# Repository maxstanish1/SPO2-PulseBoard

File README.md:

# SPO2-PulseBoard
A custom heart rate and SpO2 monitor built on an Arduino Uno R3 with a MAX30105 sensor and SSD1306 OLED display. Features a custom PCB, mode-switching buttons, and an alarm LED. Uses lightweight R-ratio SpO2 calculation and peak-detection heart rate — all tuned to run within the Arduino Uno's RAM limits.

# PulseBoard

A custom heart rate and SpO2 monitor built on an Arduino Uno R3 with a MAX30105 sensor and SSD1306 OLED display. Features a custom PCB, mode-switching buttons, and an alarm LED. Uses lightweight R-ratio SpO2 calculation and peak-detection heart rate — all tuned to run within the Arduino Uno's RAM limits.

---

## Hardware

| Component | Details |
|-----------|---------|
| Microcontroller | Arduino Uno R3 |
| Sensor | MAX30105 optical heart rate / SpO2 |
| Display | SSD1306 128×32 OLED (I2C) |
| PCB | Custom — see `/hardware` for Gerber files |

### Pin Map

| Pin | Function |
|-----|----------|
| D2 | Menu button — cycles between Heart Rate and SpO2 mode |
| D3 | Up button — reserved for future use |
| D4 | Down button — reserved for future use |
| D12 | Alarm LED — flashes when no finger is on the sensor |
| SDA / SCL | Shared I2C bus → MAX30105 + SSD1306 |

### Button Circuit
All three buttons are active-low, held HIGH by 1kΩ pull-up resistors (R1, R2, R3) with 100nF decoupling capacitors for hardware debounce. The alarm LED is driven through a 1kΩ current-limiting resistor (R4).

---

## Features

- **Heart Rate (BPM)** — peak detection on a rolling IR signal window with a 4-beat rolling average
- **SpO2 (%)** — R-ratio method with a quadratic calibration formula for accurate readings in the healthy range
- **Mode switching** — press D2 to toggle between Heart Rate and SpO2 mode; a splash screen confirms the switch
- **Alarm LED** — flashes at 1Hz on D12 when no finger is detected, turns off immediately when a finger is placed
- **Stable display** — 500ms refresh throttle prevents flicker; readings are held back for the first few seconds until the signal stabilizes

---

## How It Works

### Finger Detection
The sketch polls the MAX30105 every loop. An IR value above 50,000 indicates a finger is present (tissue absorbs the light). Below that threshold, the sensor is reading open air. All HR and SpO2 state resets on each new finger placement.

### Heart Rate Detection
A 10-sample rolling window tracks the IR signal's min, max, and range. Beat detection fires when the signal crosses 50% of the range, subject to these parameters:

| Parameter | Value |
|-----------|-------|
| Threshold | 50% of signal range |
| Minimum signal range | 400 |
| Minimum time between beats | 400ms |
| First beat | Always skipped (timing invalid) |
| Valid BPM range | 50 – 120 |
| Rolling average | 4 beats |
| Avg display delay | 8 seconds |

### SpO2 Calculation
AC (peak-to-peak) and DC (midpoint) values are computed for both the Red and IR channels from the same 10-sample window. The R-ratio is calculated as:

```
R = (redAC / redDC) / (irAC / irDC)
```

R is then passed through a quadratic calibration formula fitted to empirical blood oxygen absorption data:

```
SpO2 = -45.060 × R² + 30.354 × R + 94.845
```

The result is clamped between 70–100% and smoothed with a 9-reading rolling average. Readings are displayed after 5 seconds.

> **Note:** This formula is accurate in the healthy range (95–100%). Readings below ~90% should be treated as approximate — the sensor is not designed for clinical low-SpO2 accuracy.

---

## Libraries Required

Install these through the Arduino IDE Library Manager before compiling:

- [Adafruit SSD1306](https://github.com/adafruit/Adafruit_SSD1306)
- [Adafruit GFX](https://github.com/adafruit/Adafruit-GFX-Library)
- [SparkFun MAX3010x](https://github.com/sparkfun/SparkFun_MAX3010x_Sensor_Library) — provides `MAX30105.h`

> **Note:** This project does NOT use `spo2_algorithm.h`. That library was tested but exceeded the Uno's available RAM. SpO2 logic here is a custom lightweight implementation.

---

## Usage

1. Wire up the hardware according to the pin map above or use the custom PCB
2. Install the required libraries
3. Upload `heart_monitor.ino` to your Arduino Uno R3
4. Place your finger **lightly** on the sensor — pressing too hard flattens the pulse waveform and stops beat detection
5. Press **D2** to switch between Heart Rate and SpO2 mode
6. Wait 8 seconds for a stable heart rate average, or 5 seconds for an SpO2 reading

---

## Known Limitations

- **Finger pressure is critical** — too much pressure drops the signal range below 400 and halts detection
- **INT pin unused** — the MAX30105 interrupt pin is wired on the PCB but unconnected in firmware. Currently the sketch polls the sensor every loop. Future enhancement: wire INT to D7 for event-driven reads
- **SpO2 accuracy** — reliable in the 95–100% range; not suitable for clinical use
- **BPM range** — capped at 50–120 BPM; athletes with resting HR below 50 will see no reading

---

## Project Structure

```
PulseBoard/
├── firmware/
│   └── heart_monitor.ino
├── hardware/
│   └── (Gerber files, schematic)
└── README.md
```

---

## License

MIT

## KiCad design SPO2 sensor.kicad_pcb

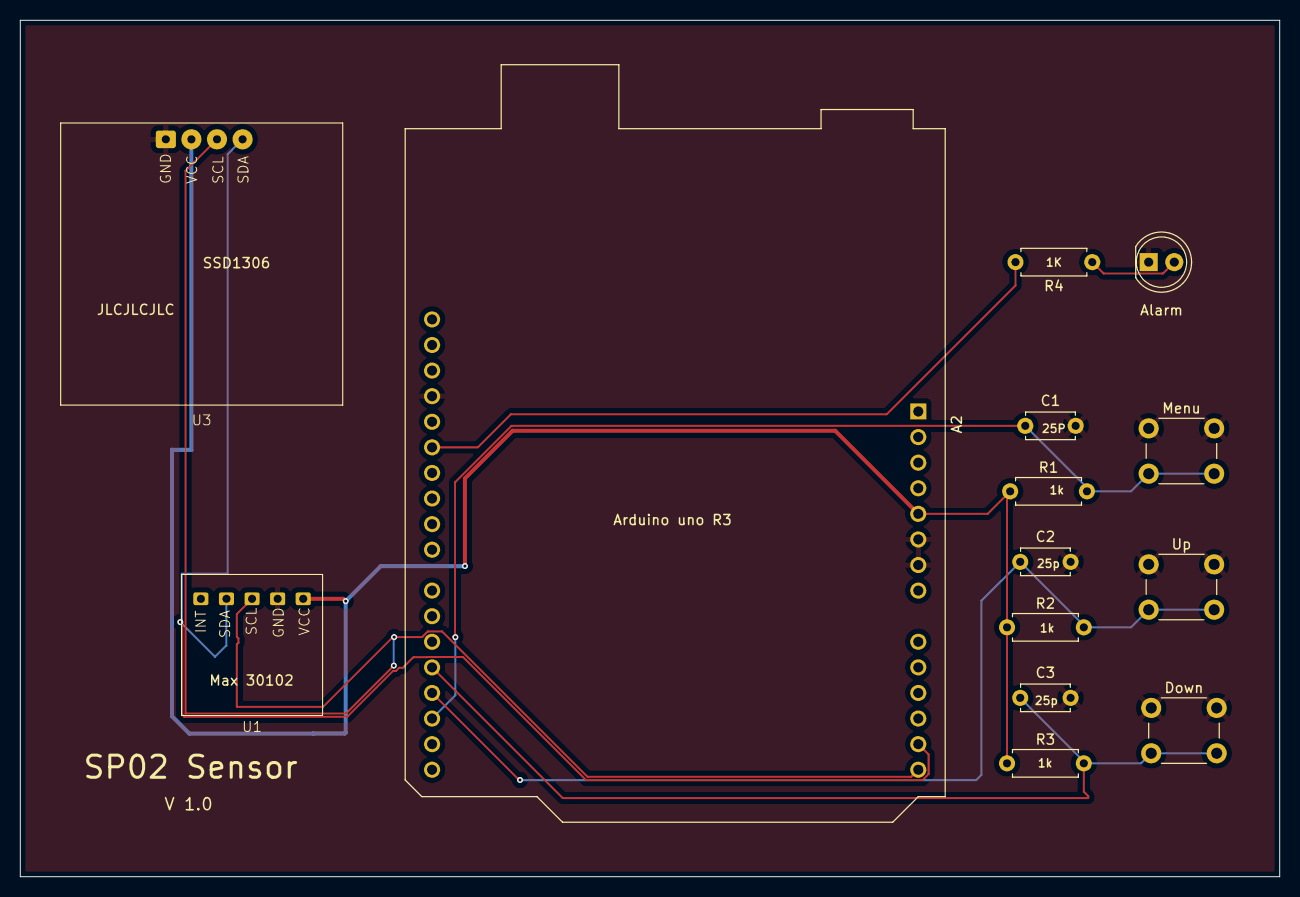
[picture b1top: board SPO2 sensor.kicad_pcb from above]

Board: 2 copper layers, 125.0 x 85.0 mm, 14 parts (0 on the bottom side), 9 nets.

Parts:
A2: Arduino_UNO_R3
Alarm: LED; LED_D5.0mm
C1, C2, C3: 100n; C_Disc_D4.7mm_W2.5mm_P5.00mm
Down: SW_Push; SW_PUSH_6mm
Menu: SW_Push; SW_PUSH_6mm
R1, R2, R3, R4: 1k; R_Axial_DIN0207_L6.3mm_D2.5mm_P7.62mm_Horizontal
U1: max 30102; spo2 max30102
U3: SSD1306
Up: SW_Push; SW_PUSH_6mm

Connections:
+5V: A2.5 (+5V), R1.1, R2.1, R3.1, U1.5 (VCC), U3.2 (SCL)
GND: A2.6 (GND), A2.7 (GND), A2.29 (GND), Alarm.1 (K), C1.2, C2.2, C3.2, Down.1, Menu.1, U1.4 (GND), U3.1 (Vcc), Up.1
unnamed: A2.17 (D2), C1.1, Menu.2, R1.2
unnamed: A2.18 (D3), C2.1, R2.2, Up.2
unnamed: A2.19 (D4), C3.1, Down.2, R3.2
unnamed: A2.27 (D12), R4.2
unnamed: Alarm.2 (A), R4.1
unnamed: A2.14 (SCL/A5), U1.3 (SCL), U3.3 (SDA)
unnamed: A2.13 (SDA/A4), U1.2 (SDA), U3.4 (GND)

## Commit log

2026-05-07 Enhance README with detailed project information
    Expanded the README.md to include detailed hardware specifications, features, usage instructions, known limitations, and project structure.
2026-05-07 Add image to README for visual enhancement
    Added an image to the README for better visual representation.
2026-05-07 Create Gerber files
2026-05-07 Update Gerber files
2026-05-07 SPO2 gerber files and board layout PNG
2026-05-07 Update README to replace 'Elegoo Uno R3' with 'Arduino Uno R3'
2026-05-07 SPO2 block diagram
    PulseBoard accepts a 5V or 9V input, which is passed to the MAX30105 sensor and OLED display at 5V. The three tactile buttons and alarm LED also run on 5V — each button is paired with a 1kΩ pull-up r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
2026-05-07 Code used for the Arduino
